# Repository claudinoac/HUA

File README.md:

# HUA é um projeto de horta urbana automatizada que une irrigação automatizada ao reuso de materiais, incentivando e ajudando o cultivo domiciliar de alimentos.

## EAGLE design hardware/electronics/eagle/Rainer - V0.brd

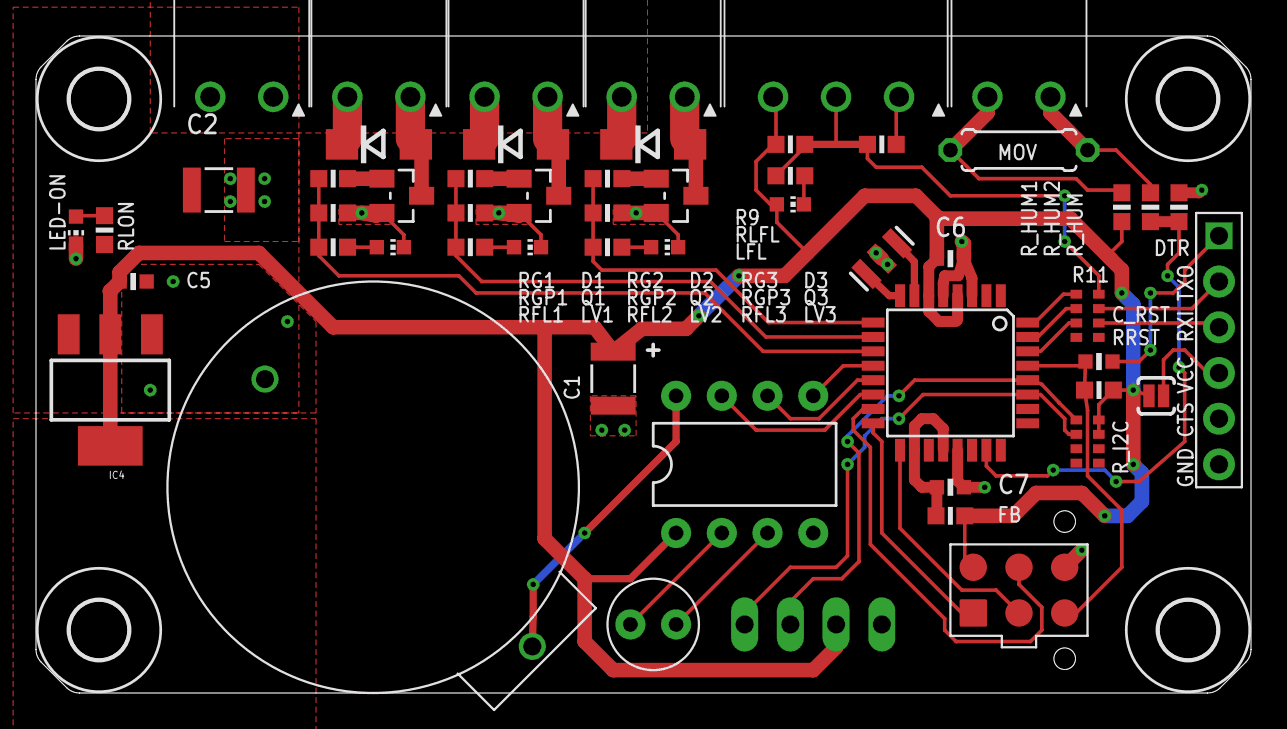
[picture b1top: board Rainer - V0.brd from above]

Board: 2 copper layers, 67.5 x 36.5 mm, 58 parts (0 on the bottom side), 43 nets.

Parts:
C1, C2: 10uF 25V; C1210
C5, C6, C7: 100nF; C0603
C_RST: 100nF; C0603
D1, D2, D3: 30V 1A; DO214AC
FB: R0603
H1, H2, H3, H4: MOUNT-HOLE3.2; 3,2
IC4: SOT223
JP5: FTDI_DEVICE; FTDI_DEVICE_SIDE
LED-ON: CHIP-LED0603
LFL: CHIP-LED0603
LV1, LV2, LV3: CHIP-LED0603
MOV: 0207/7
Q1, Q2, Q3: NFET; SOT23
R9, R10: DNP; R0603
R11: 100R; 0603-ARV
RFL1, RFL3: 4k7; R0603
RFL2: 1k; R0603
RG1, RG2, RG3: 100R; R0603
RGP1, RGP2, RGP3: 4k7; R0603
RLFL: 4k7; R0603
RLON: 4k7; R0603
RRST: 4k7; R0603
R_HUM: 100k?; R0603
R_HUM1, R_HUM2: 1k?; R0603
R_I2C: 1k; 0603-ARV
SJ1: JP; SJ_2S-NOTRACE
U1: ATMEGA328P; TQFP32-08
U$1: ISP_POGO-2HOLES; ISP_POGO
U$2: DS1302; DIL08-ROUND
U$4: CR2032; CR2032-A
X1, X2, X7, X9, X10: 1751248
X3: CONECTOR-3VIAS; 3.5MM-3VIAS
X8: 22-23-2041
Y1: TC26V
Y2: 16MHz; RESONATOR-SMD

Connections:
+5V: C1.1, C5.1, C6.1, FB.2, IC4.2, IC4.4, LFL.A, R9.2, RRST.2, R_HUM1.1, R_I2C.7, R_I2C.8, SJ1.1, U1.4, U1.6, U$1.VCC, U$2.1, X3.3, X8.2
+12V: C2.1, D1.C, D2.C, D3.C, IC4.3, RLON.2, X1.2, X7.2, X9.2, X10.2
AVCC: C7.1, FB.1, U1.18, U1.20
FLUXO: R9.1, R10.2, R11.4, RLFL.1, X3.2
GND: C1.2, C2.2, C5.2, C6.2, C7.2, IC4.1, JP5.P$5, JP5.P$6, LED-ON.C, LV1.C, LV2.C, LV3.C, Q1.2, Q2.2, Q3.2, R10.1, RGP1.1, RGP2.1, RGP3.1, R_HUM.1, U1.3, U1.5, U1.21, U$1.GND, U$2.4, U$4.P$1, X1.1, X3.1, X8.1, Y2.2
HUM_IN: R_HUM.2, R_HUM2.1, U1.23
MISO: U1.16, U$1.MISO
MOSI: U1.15, U$1.MOSI
unnamed: U1.7, Y2.1
unnamed: MOV.2, R_HUM1.2, X2.2
unnamed: U1.8, Y2.3
unnamed: MOV.1, R_HUM2.2, X2.1
unnamed: LFL.C, RLFL.2
unnamed: Q1.1, RG1.2
unnamed: LED-ON.A, RLON.1
unnamed: U$2.2, Y1.2
unnamed: U$2.3, Y1.1
unnamed: D1.A, Q1.3, X7.1
unnamed: R11.7, U1.30
unnamed: Q2.1, RG2.2
unnamed: D2.A, Q2.3, X9.1
unnamed: Q3.1, RG3.2
unnamed: D3.A, Q3.3, X10.1
unnamed: JP5.P$4, SJ1.2
unnamed: R11.6, U1.31
unnamed: R11.5, U1.32
unnamed: LV3.A, RFL3.1
unnamed: LV2.A, RFL2.1
unnamed: LV1.A, RFL1.1
RESET: C_RST.2, RRST.1, U1.29, U$1.RST
RST: C_RST.1, JP5.P$1
RTC_CE/RST: U1.12, U$2.5
RTC_IO/DAT: U1.13, U$2.6
RTC_SCLK: U1.14, U$2.7
RX: JP5.P$3, R11.2
SCK: U1.17, U$1.SCK
SCL: R_I2C.1, U1.28, X8.3
SDA: R_I2C.2, U1.27, X8.4
TX: JP5.P$2, R11.3
VALV1: RFL1.2, RG1.1, RGP1.2, U1.11
VALV2: RFL2.2, RG2.1, RGP2.2, U1.10
VALV3: RFL3.2, RG3.1, RGP3.2, U1.9
VBAT: U$2.8, U$4.P$2

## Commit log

2017-08-19 eletronica
2017-10-03 Add files via upload
    Esquema Fritzing de montagem de protoboard com medidor de umidade do solo usando monitor LCD, Potenciometro e um LED.
2017-12-11 Rename esqUmidSolo_fundino_led_LCD.ino to esqUmidSoloDESIGNRIO
2017-12-12 Add files via upload
    Aqui você encontra a programação usada no medidor de umidade do solo para a oficina HUA da PLASTCOLAB
2017-12-12 oficina HUA - PLASTCOLAB
    oficina HUA - PLASTCOLAB
    imagem esquemática de como deve ser montado o sistema para medidor de umidade do solo.
2018-04-10 Kicad SCH of Version 0.1
2018-04-12 ADD: Bill of Materials
2018-12-04 EDIT: NODEMCU as a replacement for arduino (V2)
2018-12-05 ADD: Soil Moisture Sensor circuit and Fabrication Files
2018-12-05 ADD: Soil Moisture Sensor's G-Codes
2018-12-06 EDIT: Soil Moisture Sensor's G-Codes for PCB Milling
2021-10-10 [HUA-001] refactor: move electronics and BOM files to proper directory
2021-10-10 feat: create arduino uno code in rust

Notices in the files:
parts and their libraries:
SparkFun-DiscreteSemi: Licensing: CC v3.0 Share-Alike You are welcome to use this library for commercial purposes.
